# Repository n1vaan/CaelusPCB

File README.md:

# Project Caelus Encoder PCB

### Project Description

This is a custom PCB we designed to streamline the control system for our liquid-fueled rocket tests. It combines signal encoding, ignition control, and ESP32-based automation into one board, letting us send multiple control signals through a single ethernet cable and run timed sequences automatically.

### Why we made it

Our previous setup was messy and inefficient; we had to use several long ethernet cables and manually flip switches during tests. This new design makes everything cleaner, safer, and more reliable by cutting down cable clutter and adding automated control for key parts like valves and the igniter.

## 3D Render of PCB

## Circuit Diagram of PCB

## Close up shot of PCB

## Bill of Materials (BOM)

| Component                    | Quantity  | JLCPCB Estimate  |
|------------------------------|-----------|------------------|
| PCB                          | 1         | $150             |

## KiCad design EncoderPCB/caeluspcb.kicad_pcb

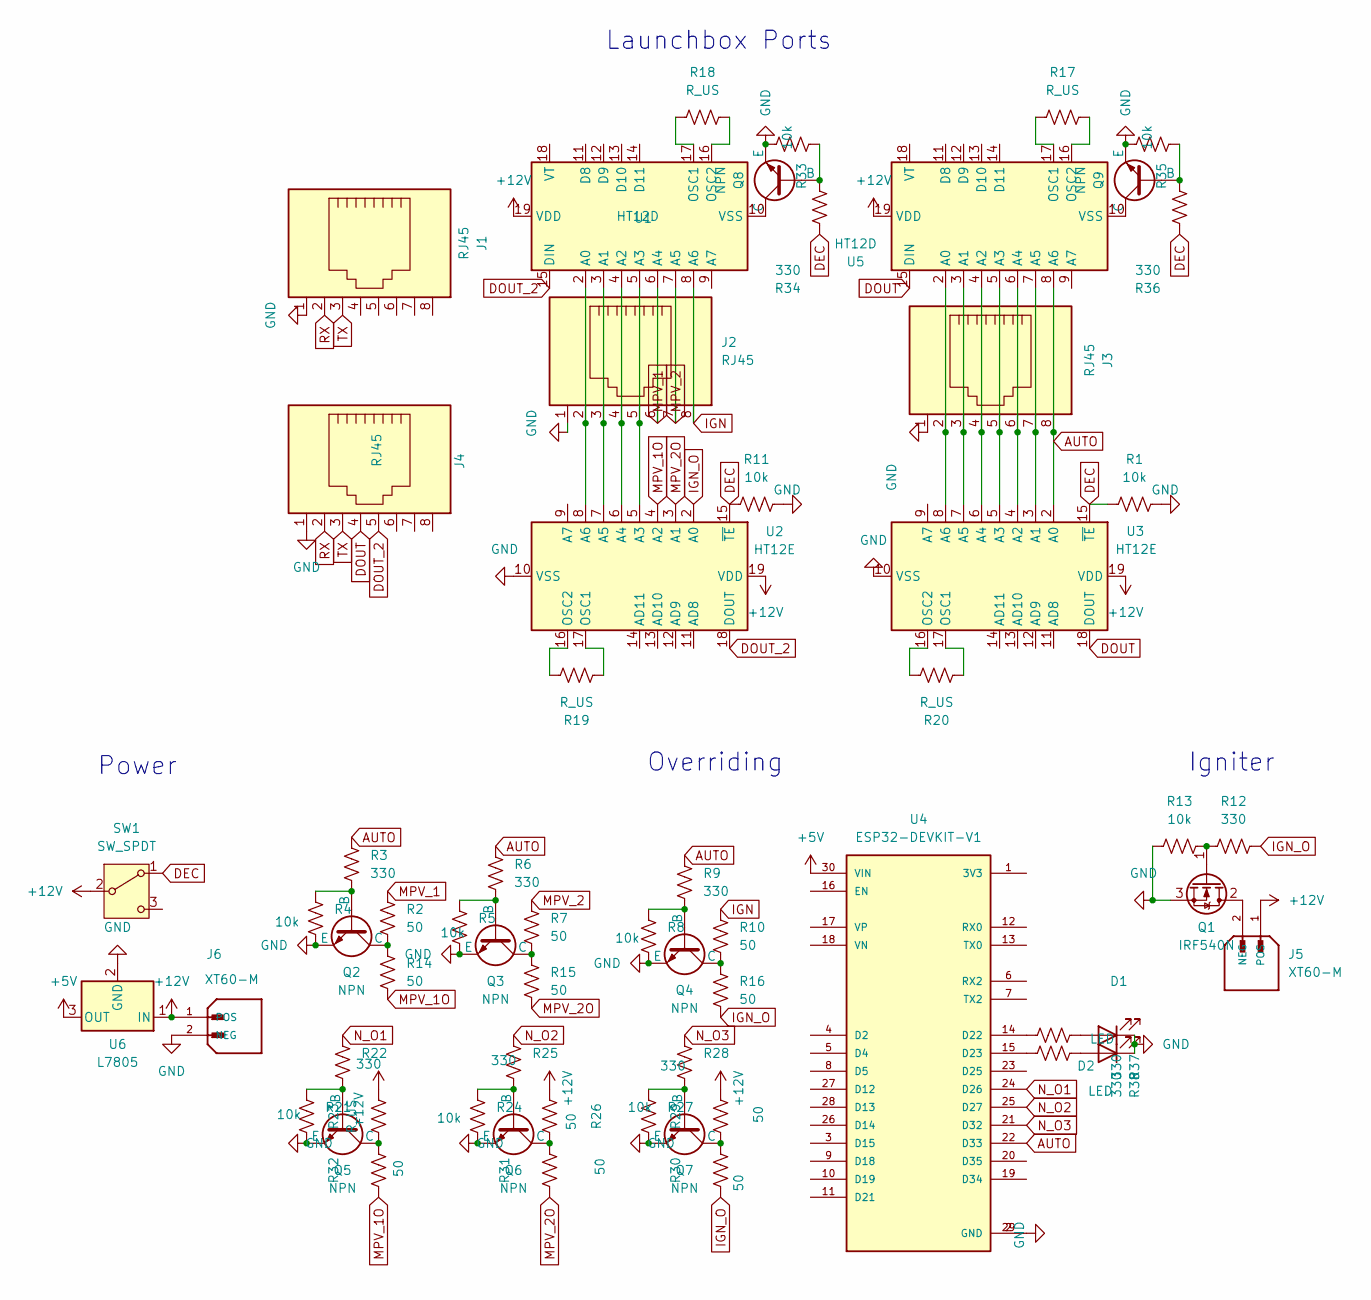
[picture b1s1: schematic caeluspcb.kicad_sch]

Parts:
D1, D2: LED; LED_D3.0mm
J1, J2, J3, J4: RJ45; RJ45_Amphenol_54602-x08_Horizontal
J5: XT60-M; JST_EH_B2B-EH-A_1x02_P2.50mm_Vertical
J6: XT60-M; AMASS_XT60-M_1x02_P7.20mm_Vertical
Q1: IRF540N; TO-220-3_Vertical
Q2, Q3, Q4, Q5, Q6, Q7, Q8, Q9: NPN; TO-92
R1, R4, R5, R8, R11, R13, R21, R24, R27, R33, R35: 10k; R_Axial_DIN0207_L6.3mm_D2.5mm_P10.16mm_Horizontal
R2, R7, R10, R14, R15, R16, R26, R29, R30, R31, R32: 50; R_Axial_DIN0207_L6.3mm_D2.5mm_P10.16mm_Horizontal
R3, R6, R9, R12, R22, R25, R28, R34, R36, R37, R38: 330; R_Axial_DIN0207_L6.3mm_D2.5mm_P10.16mm_Horizontal
R17, R18, R19, R20, R23: R_US; R_Axial_DIN0207_L6.3mm_D2.5mm_P10.16mm_Horizontal
SW1: SW_SPDT; SPDT_Slide_Switch
U1, U5: HT12D; CERDIP-18_W7.62mm_SideBrazed
U2, U3: HT12E; CERDIP-18_W7.62mm_SideBrazed
U4: ESP32-DEVKIT-V1; MODULE_ESP32_DEVKIT_V1; PARTREV N/A
U6: L7805; TO-220-3_Vertical

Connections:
+5V: U4.30 (VIN), U6.3 (OUT)
+12V: J5.1 (POS), J6.1 (POS), R23.2, R26.2, R29.2, SW1.2 (B), U1.19 (VDD), U2.19 (VDD), U3.19 (VDD), U5.19 (VDD), U6.1 (IN)
AUTO: J3.8, R3.1, R6.1, R9.1, U3.2 (A0), U4.22 (D33), U5.8 (A6)
DEC: R1.1, R11.1, R34.1, R36.1, SW1.1 (A), U2.15 (~TE), U3.15 (~TE)
DOUT: J4.4, U3.18 (DOUT), U5.15 (DIN)
DOUT_2: J4.5, U1.15 (DIN), U2.18 (DOUT)
GND: D1.1 (K), D2.1 (K), J1.1, J2.1, J3.1, J4.1, J6.2 (NEG), Q1.3 (S), Q2.3 (E), Q3.3 (E), Q4.3 (E), Q5.3 (E), Q6.3 (E), Q7.3 (E), Q8.3 (E), Q9.3 (E), R1.2, R4.2, R5.2, R8.2, R11.2, R13.1, R21.2, R24.2, R27.2, R33.2, R35.2, U2.10 (VSS), U3.10 (VSS), U4.2 (GND), U4.29 (GND), U6.2 (GND)
IGN: J2.8, R10.1, U1.8 (A6)
IGN_O: R12.2, R16.2, R30.1, U2.2 (A0)
MPV_1: J2.6, R2.1, U1.6 (A4)
MPV_1O: R14.2, R32.1, U2.4 (A2)
MPV_2: J2.7, R7.1, U1.7 (A5)
MPV_2O: R15.2, R31.1, U2.3 (A1)
N_O1: R22.1, U4.24 (D26)
N_O2: R25.1, U4.25 (D27)
N_O3: R28.1, U4.21 (D32)
unnamed: D1.2 (A), R37.1
unnamed: D2.2 (A), R38.1
unnamed: J5.2 (NEG), Q1.2 (D)
unnamed: Q1.1 (G), R12.1, R13.2
unnamed: Q2.2 (B), R3.2, R4.1
unnamed: Q2.1 (C), R2.2, R14.1
unnamed: Q3.2 (B), R5.1, R6.2
unnamed: Q3.1 (C), R7.2, R15.1
unnamed: Q4.2 (B), R8.1, R9.2
unnamed: Q4.1 (C), R10.2, R16.1
unnamed: Q5.2 (B), R21.1, R22.2
unnamed: Q5.1 (C), R23.1, R32.2
unnamed: Q6.2 (B), R24.1, R25.2
unnamed: Q6.1 (C), R26.1, R31.2
unnamed: Q7.2 (B), R27.1, R28.2
unnamed: Q7.1 (C), R29.1, R30.2
unnamed: Q8.2 (B), R33.1, R34.2
unnamed: Q8.1 (C), U1.10 (VSS)
unnamed: Q9.2 (B), R35.1, R36.2
unnamed: Q9.1 (C), U5.10 (VSS)
unnamed: J2.2, U1.2 (A0), U2.8 (A6)
unnamed: J2.3, U1.3 (A1), U2.7 (A5)
unnamed: J2.4, U1.4 (A2), U2.6 (A4)
unnamed: J2.5, U1.5 (A3), U2.5 (A3)
unnamed: R18.2, U1.17 (OSC1)
unnamed: R18.1, U1.16 (OSC2)
unnamed: R19.2, U2.17 (OSC1)
unnamed: R19.1, U2.16 (OSC2)
unnamed: J3.7, U3.3 (A1), U5.7 (A5)
unnamed: J3.6, U3.4 (A2), U5.6 (A4)
unnamed: J3.5, U3.5 (A3), U5.5 (A3)
unnamed: J3.4, U3.6 (A4), U5.4 (A2)
unnamed: J3.3, U3.7 (A5), U5.3 (A1)
unnamed: J3.2, U3.8 (A6), U5.2 (A0)
unnamed: R20.2, U3.17 (OSC1)
unnamed: R20.1, U3.16 (OSC2)
unnamed: R37.2, U4.14 (D22)
unnamed: R38.2, U4.15 (D23)
unnamed: R17.2, U5.17 (OSC1)
unnamed: R17.1, U5.16 (OSC2)
RX: J1.2, J4.2
TX: J1.3, J4.3

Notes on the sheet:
Power
Igniter
Overriding
Launchbox Ports

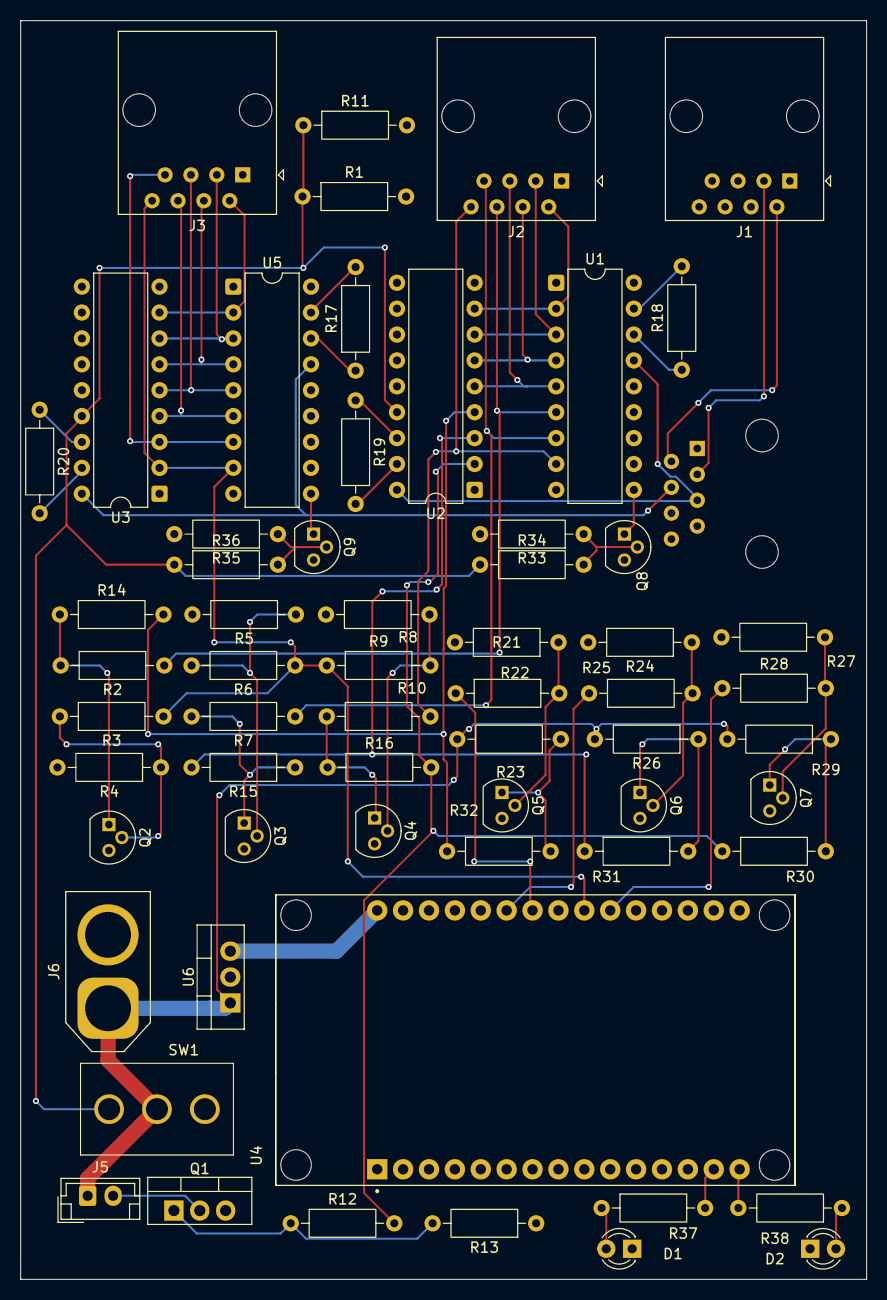
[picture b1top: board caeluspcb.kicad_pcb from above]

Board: 2 copper layers, 83.0 x 123.5 mm, 62 parts (1 on the bottom side), 58 nets.

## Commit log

2025-06-15 Create f
2025-06-15 Add EncoderPCB contents
2025-06-15 Deleted EncoderPCB
2025-06-16 Added Image
2025-06-16 5/20 Progress
2025-06-16 asdfj
2025-06-16 526img
2025-06-16 image
